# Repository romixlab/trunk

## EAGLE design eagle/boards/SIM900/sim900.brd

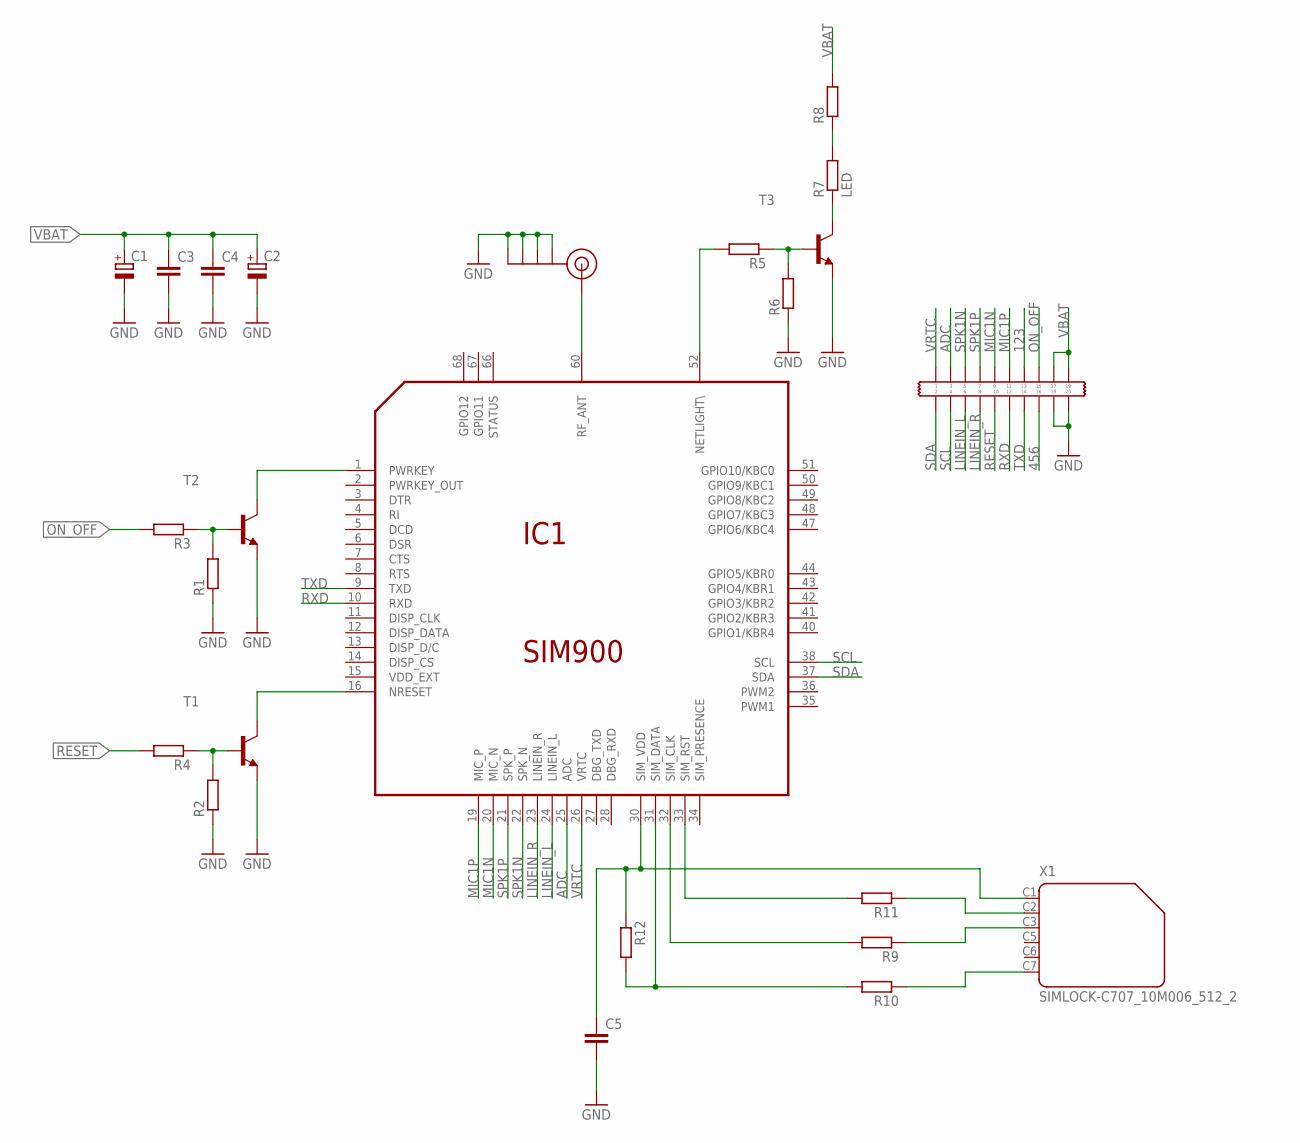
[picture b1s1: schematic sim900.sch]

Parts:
C1, C2: CPOL-EUSMCD; SMC_D
C3, C4: C-EUC0805K; C0805K
C5: C-EUC1206K; C1206K
IC1: SIM900
J$1: SMA_EDGE; SMA-EDGE
R1, R2, R3, R4, R5, R6, R8, R9, R10, R11, R12: R-EU_R0805; R0805
R7: LED; R0805
T1, T2, T3: -NPN-SOT23-EBC; SOT23-EBC
U$1: 2X10
X1: SIMLOCK-C707_10M006_512_2; C707_10M006_512_2

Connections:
123: U$1.T13 (C13)
456: U$1.B16 (C16)
ADC: IC1.25 (ADC), U$1.T3 (C3)
GND: C1.-, C2.-, C3.2, C4.2, C5.2, IC1.17 (GND), IC1.18 (GND), IC1.29 (GND), IC1.39 (GND), IC1.45 (GND), IC1.46 (GND), IC1.53 (GND), IC1.54 (GND), IC1.58 (GND), IC1.59 (GND), IC1.61 (GND), IC1.62 (GND), IC1.63 (GND), IC1.64 (GND), IC1.65 (GND), J$1.GND@0 (GND), J$1.GND@1 (GND), J$1.GND@2 (GND), J$1.GND@3 (GND), R1.1, R2.1, R6.1, T1.E, T2.E, T3.E, U$1.B18 (C18), U$1.B20 (C20)
LINEIN_L: IC1.24 (LINEIN_L), U$1.B6 (C6)
LINEIN_R: IC1.23 (LINEIN_R), U$1.B8 (C8)
MIC1N: IC1.20 (MIC_N), U$1.T9 (C9)
MIC1P: IC1.19 (MIC_P), U$1.T11 (C11)
unnamed: IC1.60 (RF_ANT), J$1.SIG (SIGNAL)
unnamed: IC1.1 (PWRKEY), T2.C
unnamed: IC1.16 (NRESET), T1.C
unnamed: R2.2, R4.1, T1.B
unnamed: R1.2, R3.1, T2.B
unnamed: C5.1, IC1.30 (SIM_VDD), R12.1, X1.C1 (1)
unnamed: R7.2, R8.1
unnamed: R5.1, R6.2, T3.B
unnamed: IC1.52 (NETLIGHT\), R5.2
unnamed: R7.1, T3.C
unnamed: R11.1, X1.C2 (2)
unnamed: IC1.33 (SIM_RST), R11.2
unnamed: R9.1, X1.C3 (3)
unnamed: R10.1, X1.C7 (6)
unnamed: IC1.32 (SIM_CLK), R9.2
unnamed: IC1.31 (SIM_DATA), R10.2, R12.2
ON_OFF: R3.2, U$1.T15 (C15)
RESET: R4.2, U$1.B10 (C10)
RXD: IC1.10 (RXD), U$1.B12 (C12)
SCL: IC1.38 (SCL), U$1.B4 (C4)
SDA: IC1.37 (SDA), U$1.B2 (C2)
SPK1N: IC1.22 (SPK_N), U$1.T5 (C5)
SPK1P: IC1.21 (SPK_P), U$1.T7 (C7)
TXD: IC1.9 (TXD), U$1.B14 (C14)
VBAT: C1.+, C2.+, C3.1, C4.1, IC1.55 (VBAT), IC1.56 (VBAT), IC1.57 (VBAT), R8.2, U$1.T17 (C17), U$1.T19 (C19)
VRTC: IC1.26 (VRTC), U$1.T1 (C1)

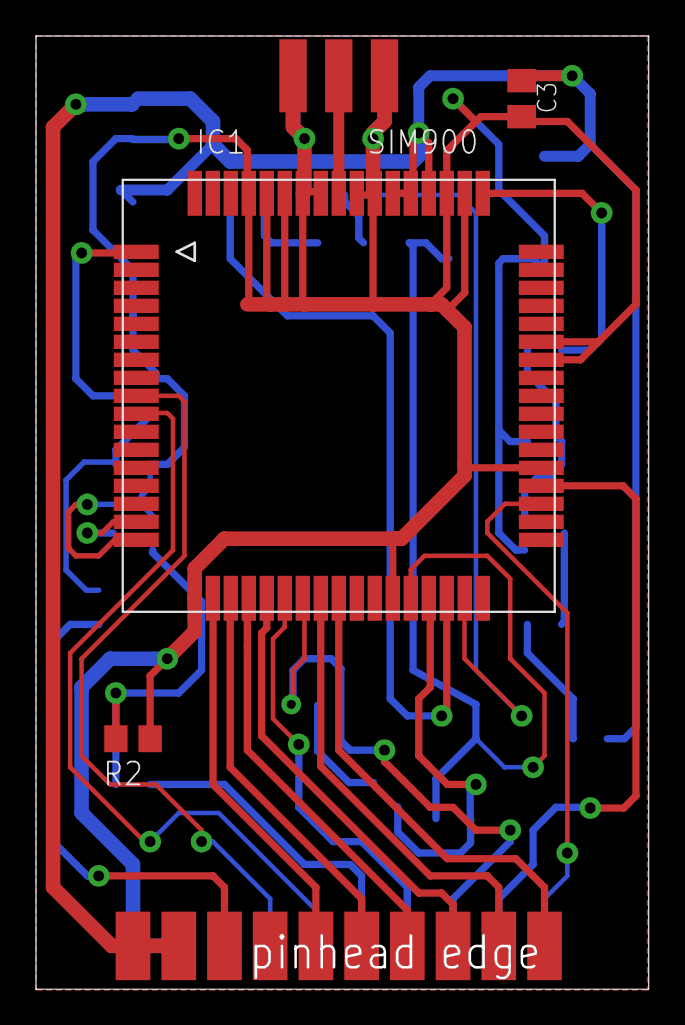
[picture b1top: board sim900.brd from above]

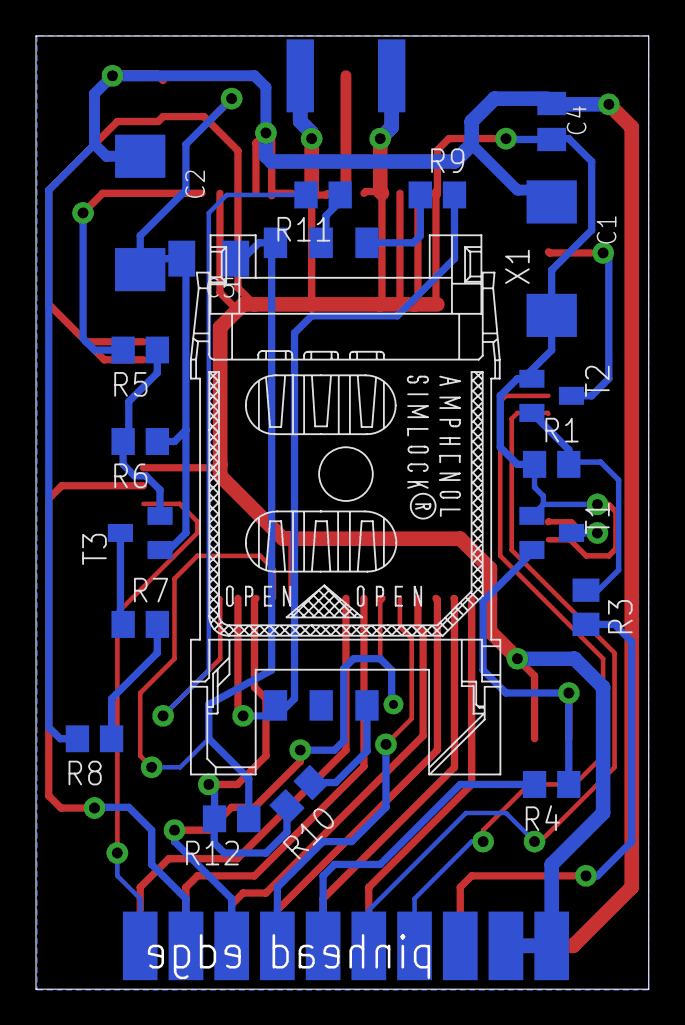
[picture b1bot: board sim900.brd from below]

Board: 2 copper layers, 34.0 x 53.0 mm, 24 parts (19 on the bottom side), 32 nets.

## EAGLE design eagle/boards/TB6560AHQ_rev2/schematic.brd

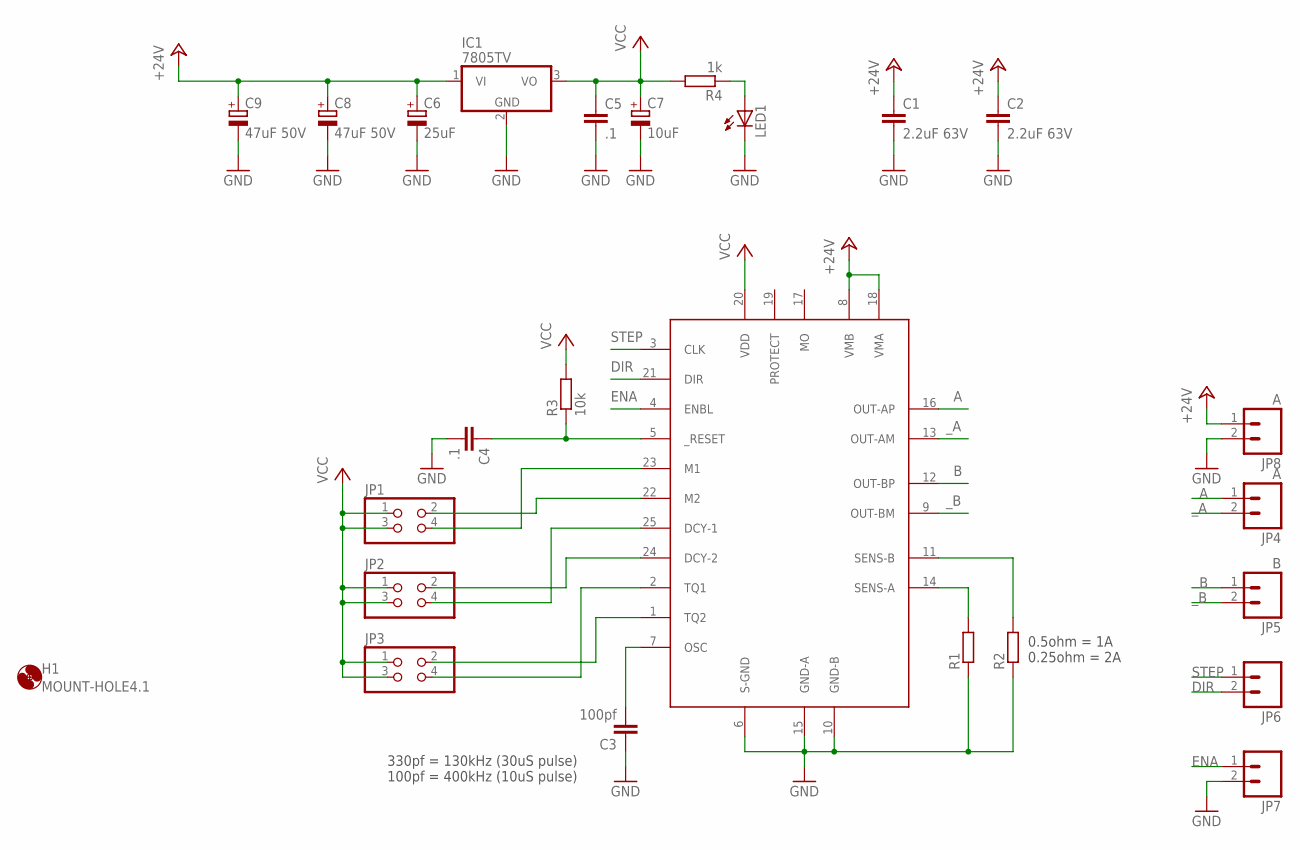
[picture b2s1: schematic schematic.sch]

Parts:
C1, C2: 2.2uF 63V; C225-108X268
C3: 100pf; C0805K
C4, C5: .1; C0805K
C6: 25uF; E2,5-5
C7: 10uF; E2,5-5
C8, C9: 47uF 50V; E2,5-5
H1: MOUNT-HOLE4.1; 4,1
IC1: 7805TV; TO220V
JP1, JP2, JP3: PINHD-2X2; 2X02
JP4, JP8: A; 1X02_XTRA_BIG
JP5: B; 1X02_XTRA_BIG
JP6, JP7: M02POGO_PIN_HOLES_ONLY; 1X02_PP_HOLES_ONLY
LED1: TLLG4400; LED3MM
R1, R2: R-EU_0617/17; 0617/17
R3: 10k; R0805
R4: 1k; R0805
U$1: TB6560-H; ZIP25-H

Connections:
+24V: C1.1, C2.1, C6.+, C8.+, C9.+, IC1.1 (VI), JP8.1, U$1.8 (VMB), U$1.18 (VMA)
A: JP4.1, U$1.16 (OUT-AP)
B: JP5.1, U$1.12 (OUT-BP)
DIR: JP6.2, U$1.21 (DIR)
ENA: JP7.1, U$1.4 (ENBL)
GND: C1.2, C2.2, C3.1, C4.2, C5.2, C6.-, C7.-, C8.-, C9.-, IC1.2 (GND), JP7.2, JP8.2, LED1.K (C), R1.1, R2.1, U$1.6 (S-GND), U$1.10 (GND-B), U$1.15 (GND-A)
unnamed: R1.2, U$1.14 (SENS-A)
unnamed: R2.2, U$1.11 (SENS-B)
unnamed: JP3.2, U$1.1 (TQ2)
unnamed: JP3.4, U$1.2 (TQ1)
unnamed: JP2.2, U$1.24 (DCY-2)
unnamed: JP2.4, U$1.25 (DCY-1)
unnamed: JP1.2, U$1.22 (M2)
unnamed: JP1.4, U$1.23 (M1)
unnamed: C4.1, R3.1, U$1.5 (_RESET)
unnamed: C3.2, U$1.7 (OSC)
unnamed: LED1.A, R4.1
STEP: JP6.1, U$1.3 (CLK)
VCC: C5.1, C7.+, IC1.3 (VO), JP1.1, JP1.3, JP2.1, JP2.3, JP3.1, JP3.3, R3.2, R4.2, U$1.20 (VDD)
_A: JP4.2, U$1.13 (OUT-AM)
_B: JP5.2, U$1.9 (OUT-BM)

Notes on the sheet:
0.5ohm = 1A 0.25ohm = 2A
330pf = 130kHz (30uS pulse) 100pf = 400kHz (10uS pulse)

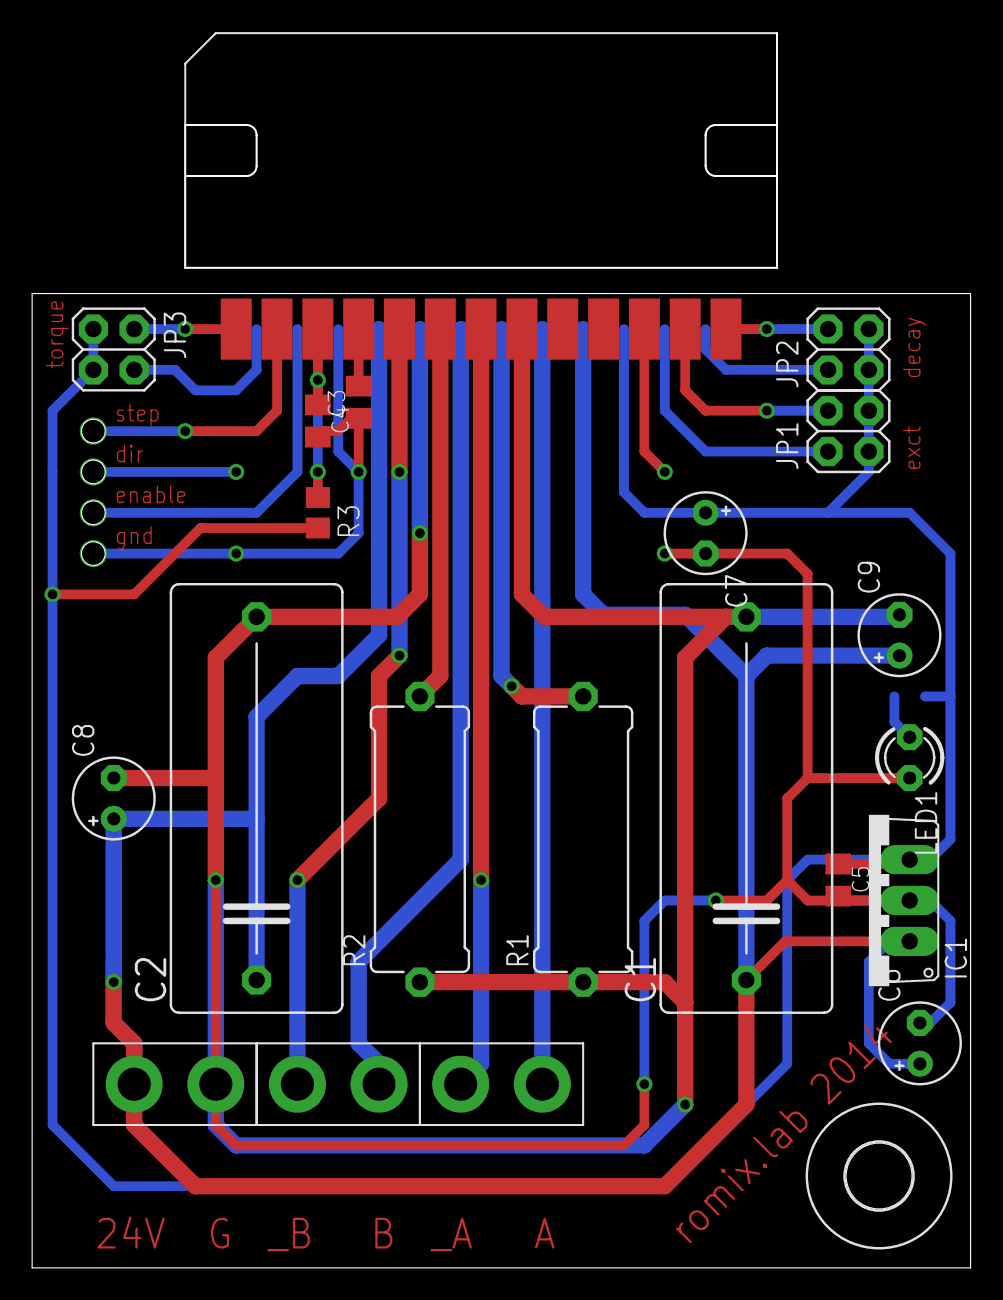
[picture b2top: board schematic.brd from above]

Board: 2 copper layers, 58.4 x 60.6 mm, 25 parts (1 on the bottom side), 21 nets.

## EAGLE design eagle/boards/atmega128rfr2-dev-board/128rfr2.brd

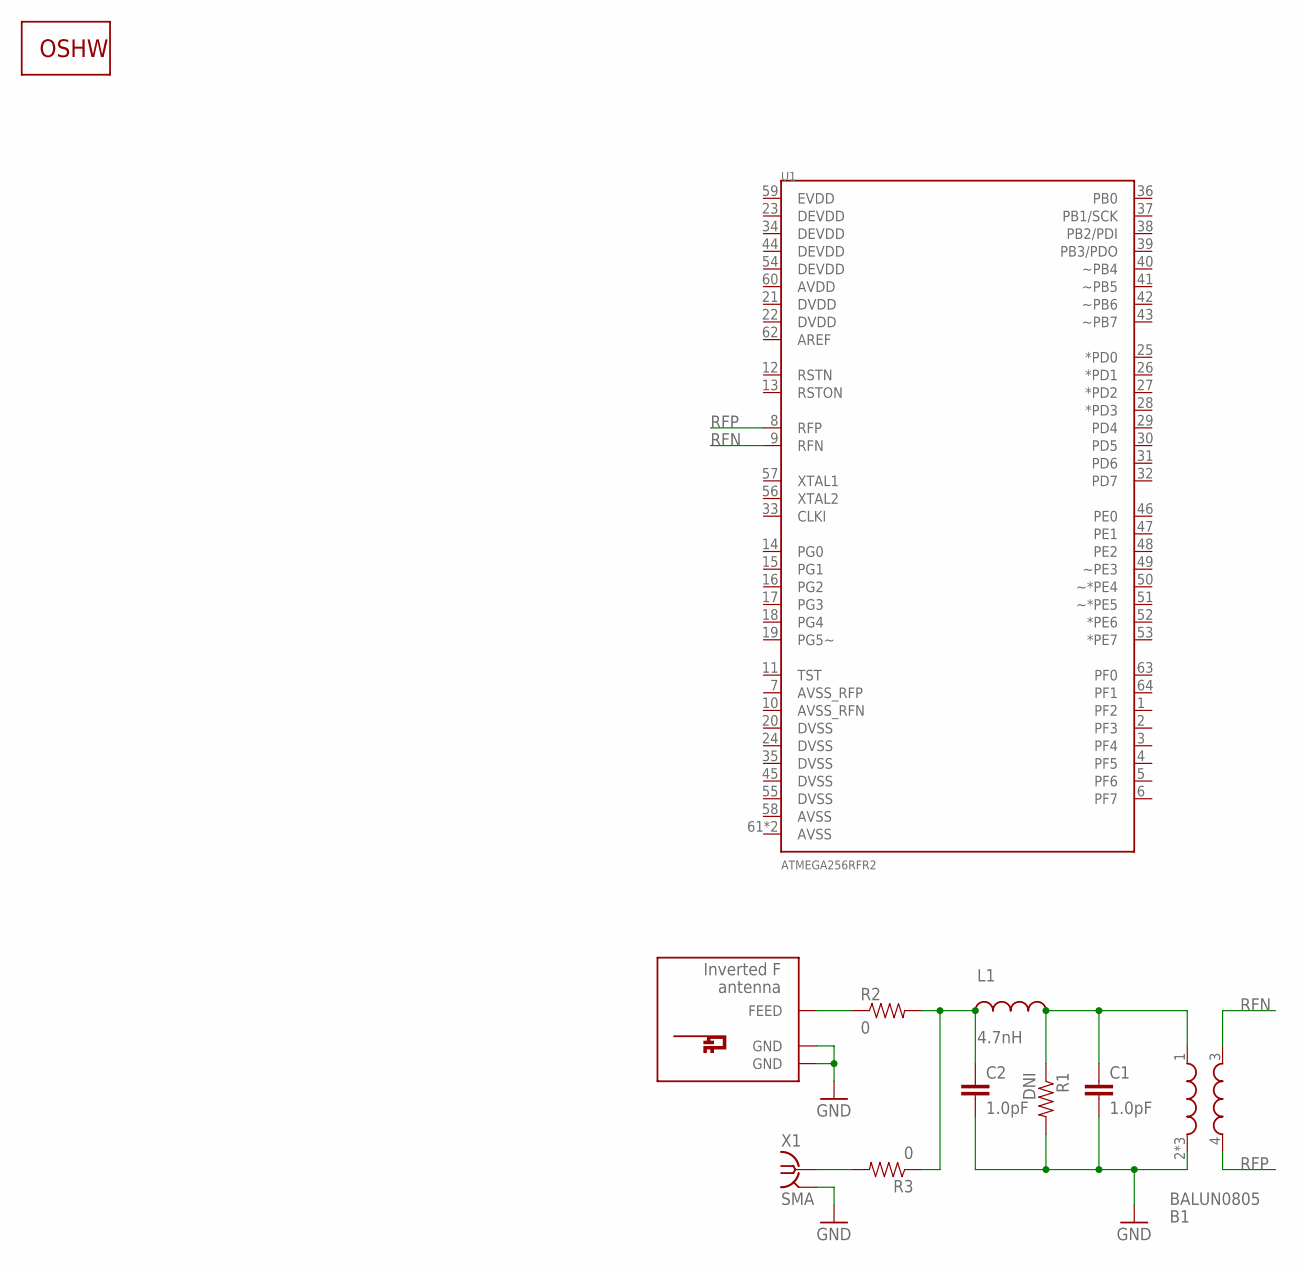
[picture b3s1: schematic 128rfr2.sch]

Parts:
B1: BALUN0805; BALUN-2-4GHZ
C1, C2: 1.0pF; 0402-CAP
L1: 4.7nH; 0402-CAP
R1: DNI; 0402-RES
R2, R3: 0; 0402-RES
U1: ATMEGA256RFR2; QFN-64
U$1: INVERTED_F_ANTENNA+5; DN007+5
U$2: LOGO-OSHWCOPPER; LOGO-OSHW-COPPER
X1: SMA; J502-ND-142-0701-801/806

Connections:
GND: B1.2 (GND), B1.5 (GND), B1.6 (GND), C1.2, C2.2, R1.2, U$1.GND, U$1.GND@1 (GND), X1.G@1 (2), X1.G@2 (2), X1.G@3 (2), X1.G@4 (2)
unnamed: R2.1, U$1.FEED
unnamed: B1.1 (IN), C1.1, L1.2, R1.1
unnamed: C2.1, L1.1, R2.2, R3.1
unnamed: R3.2, X1.1
RFN: B1.3 (OUT1), U1.9 (RFN)
RFP: B1.4 (OUT2), U1.8 (RFP)

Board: 2 copper layers, 11 parts (0 on the bottom side), 7 nets, no tracks yet.

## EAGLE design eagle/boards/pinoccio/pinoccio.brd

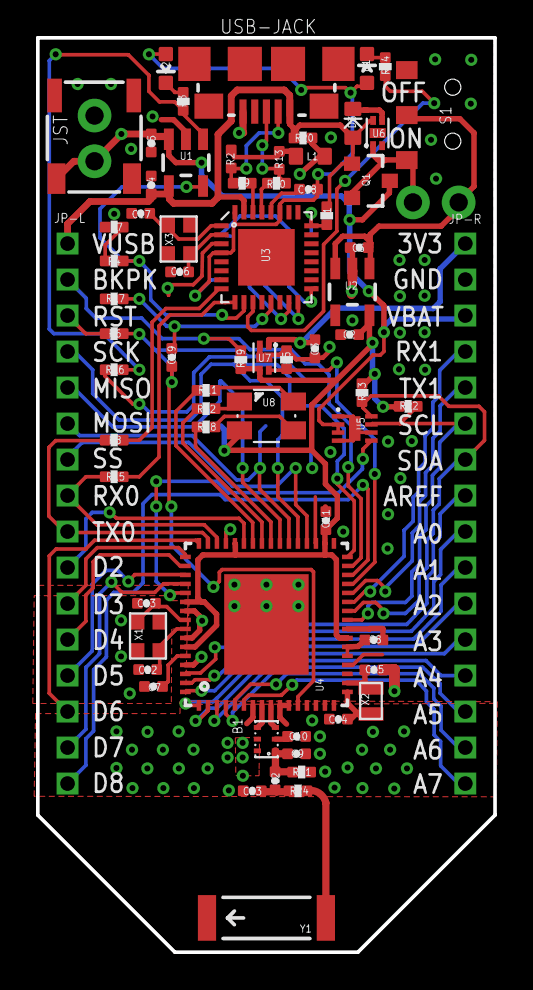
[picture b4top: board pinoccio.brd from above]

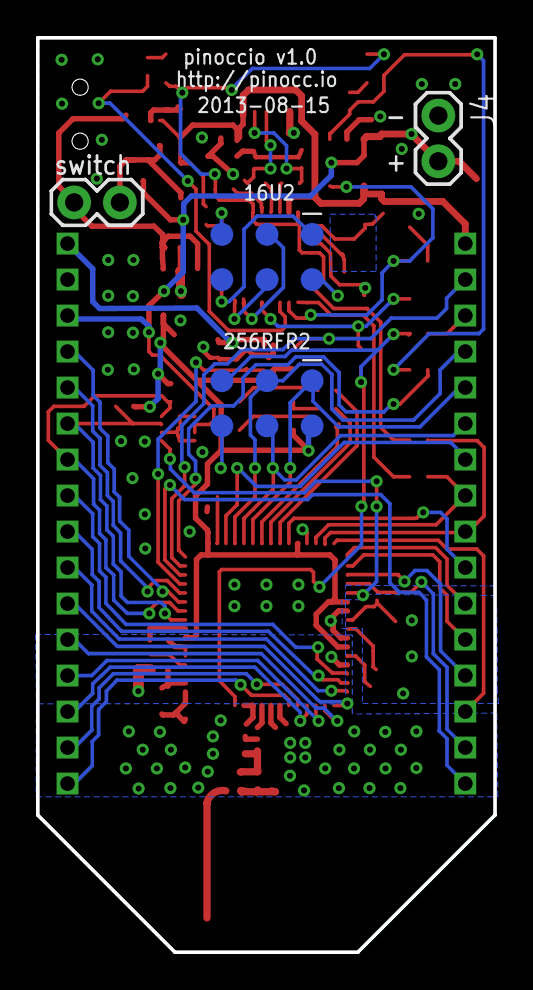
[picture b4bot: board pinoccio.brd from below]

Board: 2 copper layers, 25.4 x 50.8 mm, 71 parts (4 on the bottom side), 79 nets.

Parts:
B1: BALUN
C2, C11: 2.2uF; 0402-CAP
C3, C19: 0.1uF; 0402-CAP
C4, C5: 4.7uF; 0402-CAP
C6, C7, C8, C18: 1.0uF; 0402-CAP
C9, C23: 1.0pF; 0402-CAP
C10: DNI; 0402-CAP
C12, C13, C16, C17: 10pF; 0402-CAP
C14, C15: 12pF; 0402-CAP
D1: Green; LED-0603
D2: Yellow; LED-0603
D3: 0603-DIODE
J1: AVR_SPI_PRG_6; 2X3-PAD
J2: AVR_SPI; 2X3-PAD
J3: Switch; 1X02
J4: Ext Battery; 1X02
JP-L: M162MM; 1X16_2MM
JP-R: M162MM; 1X16_2MM
JST: JST-SFH
L1: BEAD; 0603
L2: 4.7nH; 0402-CAP
Q1: PFET; SOT23-3
R1, R4, R16, R22, R23: 2K; 0402-RES
R2, R13: VAR; 0402
R3, R6, R11, R12, R14, R18: 470; 0402-RES
R5, R20: 100k; 0402-RES
R7, R8, R15, R17: 1K; 0402-RES
R9, R10: 22; 0402-RES
R19: 100K; 0402-RES
R21: DNI; 0402-RES
R24: 0; 0402-RES
S1: SPST; SWITCH-SPDT-SMD
U1: MCP73832; SOT23-5
U2: TPS78233; SOT23-5
U3: ATMEGA16U2; QFN-32
U4: ATMEGA256RFR2; QFN-64
U5: MAX17048; DFN-8
U6, U7: SWITCH; TDFN4
U8: LED-RGB; PLCC4
USB-JACK: USB-MICROB
X1, X3: 16MHz; CRYSTAL-SMD-2.5X2-ABM10
X2: 32.768k; CRYSTAL-SMD-2X1.2-ABS06
Y1: ANTENNA2SMD5; ANTENNA-CHIP5

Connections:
A0: JP-R.P$9, U4.63
A1: JP-R.P$10, U4.64
A2: JP-R.P$11, U4.1
A3: JP-R.P$12, U4.2
A4: JP-R.P$13, U4.3
A5: JP-R.P$14, U4.4
A6: JP-R.P$15, U4.5
A7: JP-R.P$16, U4.6
AREF: JP-R.P$8, U4.62
BATTALRT: U4.53, U5.P$5
BKPK-BUS: JP-L.P$2, R19.2, U4.31
BKPKVCC-EN: R5.1, U4.29, U7.P$4
CHGSTATUS: R16.1, U4.32
D2: JP-L.P$10, U4.43
D3: JP-L.P$11, U4.49
D4: JP-L.P$12, U4.50
D5: JP-L.P$13, U4.51
D6: JP-L.P$14, U4.48
D7: JP-L.P$15, U4.52
D8: JP-L.P$16, U4.30
GND: B1.5, B1.6, C2.2, C3.2, C4.2, C5.2, C6.2, C7.2, C8.2, C9.2, C10.2, C11.2, C12.2, C13.2, C14.2, C15.2, C16.2, C17.2, C18.2, C23.2, J1.6, J2.6, J4.1, JP-R.P$2, JST.1, L1.1, R5.2, R7.1, R17.1, R20.2, R21.2, U1.2, U2.2, U2.4, U3.3, U3.28, U4.7, U4.10, U4.11, U4.20, U4.24, U4.33, U4.35, U4.45, U4.55, U4.58, U4.61, U4.PADDLE, U5.P$1, U5.P$4, U5.P$6, U5.P$9, U6.P$2, U6.P$5, U7.P$2, U7.P$5, USB-JACK.GND, X1.P$2, X1.P$4, X3.P$2, X3.P$4
LED-BLU: R18.1, U4.40
LED-GRN: R11.1, U4.42
LED-RED: R12.1, U4.41
MISO: J2.1, JP-L.P$5, U4.39
MOSI: J2.4, JP-L.P$6, U4.38
unnamed: R12.2, U8.P$1
unnamed: R2.1, R9.1, USB-JACK.D-
unnamed: D3.C, U6.P$3
unnamed: B1.1, C9.1, L2.1, R21.1
unnamed: R11.2, U8.P$4
unnamed: R18.2, U8.P$3
unnamed: J1.5, R1.2, U3.24
unnamed: R4.2, R7.2
unnamed: L1.2, R2.2, R13.2
unnamed: C7.1, U4.60
unnamed: R3.1, R16.2, U1.1
unnamed: B1.2, C10.1
unnamed: C12.1, U4.57, X1.P$1
unnamed: C13.1, U4.56, X1.P$3
unnamed: C14.1, U4.17, X2.P$1
unnamed: C15.1, U4.18, X2.P$2
unnamed: C16.1, U3.2, X3.P$1
unnamed: C8.1, U4.21, U4.22
unnamed: C17.1, U3.1, X3.P$3
unnamed: D2.C, R3.2
unnamed: C19.2, R17.2, U3.13
unnamed: R15.2, U3.9
unnamed: R8.2, U3.8
unnamed: C23.1, L2.2, R24.1
unnamed: R24.2, Y1.FEED
unnamed: R10.1, R13.1, USB-JACK.D+
unnamed: J3.1, Q1.2, S1.3, U6.P$1
unnamed: J1.1, U3.17
unnamed: J1.4, U3.16
unnamed: J1.3, U3.15
unnamed: R14.1, U3.11
unnamed: D1.C, R14.2
PROG: R4.1, U1.5, U3.10
RESET: C19.1, J2.5, R6.2, U4.12
RESET-EN: JP-L.P$3, R6.1
RFN: B1.3, U4.9
RFP: B1.4, U4.8
RX0: JP-L.P$8, R15.1, U4.46
RX1: JP-R.P$4, U4.27
SCK: J2.3, JP-L.P$4, U4.37
SCL: JP-R.P$6, R22.2, U4.25, U5.P$7
SDA: JP-R.P$7, R23.2, U4.26, U5.P$8
SSN: JP-L.P$7, U4.36
TX0: JP-L.P$9, R8.1, U4.47
TX1: JP-R.P$5, U4.28
UCAP: C18.1, D1.A, D2.A, J1.2, U3.4, U3.27, U3.32
USBD+: R10.2, U3.29
USBD-: R9.2, U3.30
VBAT: C5.1, J4.2, JP-R.P$3, JST.2, Q1.3, U1.3, U5.P$2, U5.P$3
VCC: C2.1, C11.1, J2.2, R19.1, R22.1, R23.1, U2.5, U4.23, U4.34, U4.44, U4.54, U4.59, U7.P$3, U8.P$2
VCC-AE: C3.1, JP-R.P$1, U7.P$1
VIN: C6.1, J3.2, S1.2, U2.1, U2.3
VUSB: C4.1, D3.A, JP-L.P$1, Q1.1, R1.1, R20.1, U1.4, U3.31, U6.P$4, USB-JACK.VBUS

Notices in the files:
eagle/boards/pinoccio/pinoccio.brd:
Licensed under CERN OHL v.1.1
parts and their libraries:
SparkFun-Connectors: Licensing: CC v3.0 Share-Alike You are welcome to use this library for commercial purposes.
